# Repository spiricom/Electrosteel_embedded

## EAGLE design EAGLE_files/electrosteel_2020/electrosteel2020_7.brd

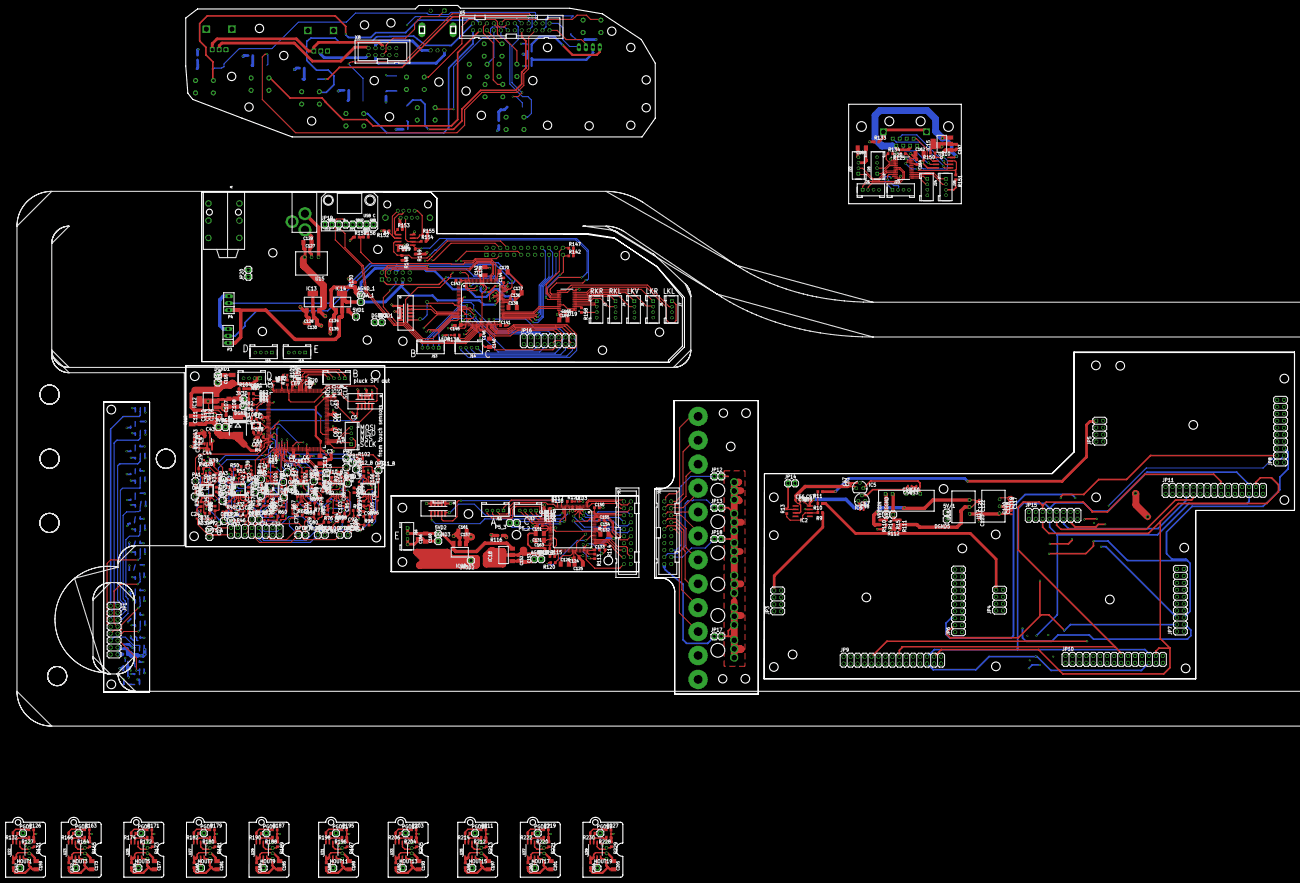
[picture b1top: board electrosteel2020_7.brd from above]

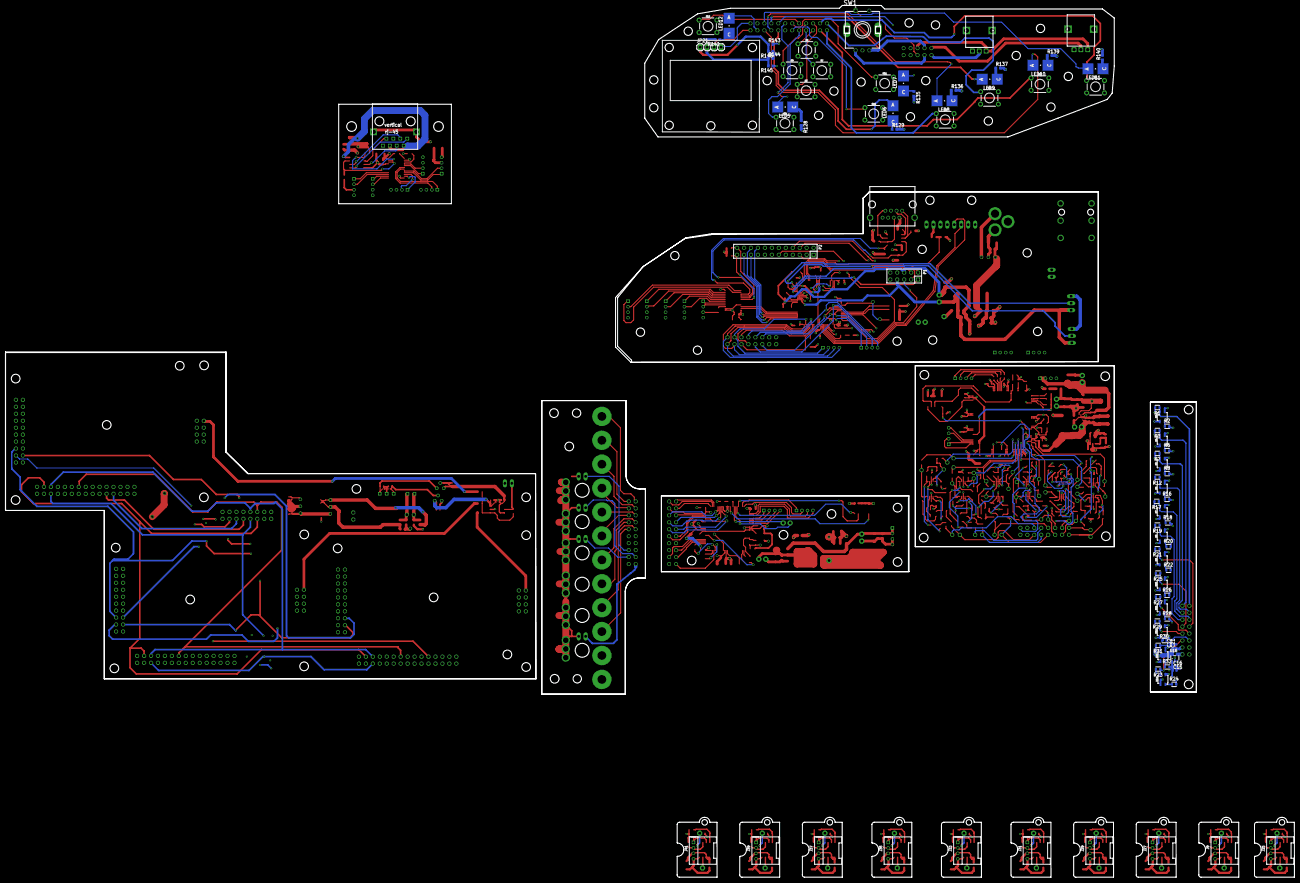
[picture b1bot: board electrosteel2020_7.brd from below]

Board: 4 copper layers, 470.7 x 318.3 mm, 606 parts (90 on the bottom side), 468 nets.

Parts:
3V3A, 3V3A_1, 3V3A_2, 3V3D, 3V3D1, 3V3D2, 5V, 5VD1, 5VD2: 1X01
5V/1: PINHD-1X1; 1X01
AGND: 1X01
AGND_1, AGND_2: 1X01
C1, C2, C3, C4, C5, C11, C12, C13, C14, C15, C20, C22, C23, C24, C25, C26, C27, C28, C29, C30, C31, C32, C33, C34, C35, C36, C37, C38, C39, C40, C41, C42, C43, C44, C45, C46, C47, C48, C49, C50, C55, C56, C57, C60, C61, C62, C63, C70, C71, C72, C73, C74, C75, C76, C77, C78, C79, C80, C81, C82, C83, C84, C85, C86, C87, C88, C89, C90, C91, C92, C93, C94, C95, C96, C97, C98, C99, C100, C101, C102, C103, C104, C105, C106, C113, C117, C118, C122, C123: .1uf; C0402
C6, C7, C8, C9, C10, C51, C52, C53, C54, C58, C59, C66, C67, C68, C69, C116, C119, C120, C121: .01uf; C0201
C16, C21, C64, C65: .01uf; C0402
C17, C18: 18pf; C0603
C19: 2.2uf; C1206
C107, C110: .1uf; C0603
C108, C111, C114: 1uf; C1206
C109, C112, C115: 10uf; SMC_B
C124, C127, C128, C133, C134, C136, C141, C142, C143, C144, C145, C146, C147, C148, C149, C150, C151, C152, C154, C156, C157, C164, C165, C166, C167, C172, C176, C180, C184, C188, C192, C196, C200, C204: .1uf; C0603K
C125, C126, C131, C132, C137, C138, C139, C140, C159, C162, C163, C169, C170, C173, C177, C181, C185, C189, C193, C197, C201, C205: 1uf; C1206K
C129, C130, C135, C153, C160, C161, C168: 10uf; C1206K
C155: 2200pf; C0603K
D3: MBRS340T3; SMC
DGND, DGND1, DGND2, DGND3: 1X01
DGND5: PINHD-1X1; 1X01
HOUT1, HOUT3, HOUT5, HOUT7, HOUT9, HOUT11, HOUT13, HOUT15, HOUT17, HOUT19: 1X01
IC1, IC7, IC8, IC9, IC10, IC17: OPA4344E; TSSOP14
IC2: OPA134D; SO08
IC3: STM32H743ZIT6; QFP50P2200X2200X160-144N
IC4: LMV321M5; SOT23-5
IC5: 78LXX
IC6: 79LXX
IC11: LP5912; 6-WSON
IC12, IC13, IC14, IC15, IC18, IC20: REG1117; SOT223
J1: AUDIO_JACK_TRS_0.25"_PTH_RA; AUDIO_JACK_0.25"_TRS_PTH_RA
J3, J4, J5, J6, J7, J8, J10, J11, J12, J13, J14, J16, J17, J18, J19, J20, J21, J22, J23, J24, J26: 4P-2.0; HW4-2.0
J9, J25, J27, J29, J31, J33, J35, J37, J39, J41: 4P-2.0-90D; HW4-2.0-90D
JP1, JP2, JP15, JP16: PINHD-2X8; 2X08
JP3, JP4, JP5: PINHD-2X4; 2X04
JP6, JP7, JP8: PINHD-2X10; 2X10
JP9, JP10, JP11: 2X15
JP12, JP13, JP14, JP17, JP18, JP20: PINHD-1X2; 1X02
JP19: PINHD-1X8; 1X08
JP21: PINHD-1X4; 1X04
LED1, LED3, LED4: RED; CHIP-LED0603
LED2: GREEN; CHIP-LED0603
LED5, LED6, LED7, LED8, LED9, LED10, LED11, LED12: P-LCC-2
OPT1_A, OPT1_B, OPT2_A, OPT2_B, OPT3_A, OPT3_B, OPT4_A, OPT4_B, OPT5_A, OPT5_B, OPT6_A, OPT6_B, OPT7_A, OPT7_B, OPT8_A, OPT8_B, OPT9_A, OPT9_B, OPT10_A, OPT10_B, OPT11_A, OPT11_B, OPT12_A, OPT12_B: PINHD-1X1; 1X01
P1: P-10-100-2X05_M; DIL-100-2X05_M
P2: P-24-100-2X12_M; DIL-100-2X12_M
P3, P4: M-1X03-SIP-100-40Y; SIP-100-03-40Y
P5_2, P5_3: 1X01
PA0, PA1, PA2, PA3, PA4, PA5, PA6, PA7: PINHD-1X1; 1X01
PB0, PB1: PINHD-1X1; 1X01
PC4, PC5: PINHD-1X1; 1X01
PGO1, PGO3, PGO5, PGO7, PGO9, PGO11, PGO13, PGO15, PGO17, PGO19: 1X01
Q1: 25MHz; NX3225
R1, R3, R7, R12, R17, R19, R21, R23, R25, R27, R29, R31: 10k; RESC1608X60
R2, R6, R8, R16, R18, R20, R22, R24, R26, R28, R30, R32: 100R; RESC1608X60
R4: 47R; R0603
R5: 10k; R0402
R9, R10, R11, R13, R125, R134, R158: 1k; R0603
R14, R15, R86, R87, R108, R132, R145, R146, R166, R174, R182, R190, R198, R206, R214, R222, R230: 0R_DNP; R0603
R33, R34, R38, R39, R45, R46, R50, R51, R55, R56, R60, R61, R66, R67, R71, R72, R76, R77, R88, R89, R93, R94, R98, R99: 20k; R0603
R35, R36, R40, R41, R47, R48, R52, R53, R57, R58, R63, R64, R68, R69, R73, R74, R78, R80, R90, R91, R95, R96, R100, R101: 820R; R0603
R37, R42, R49, R54, R59, R65, R70, R75, R82, R85, R92, R97, R102, R103, R110, R111, R112, R116, R130, R133, R143, R144: 0R; R0603
R43, R44: 100k; R0603
R62, R81, R83, R84, R117, R118, R119, R121, R122, R124: 33R; R0201
R79, R104, R123, R128, R129, R135, R136, R137, R138, R139, R140, R141: 560R; R0603
R105, R106, R107, R109: 33R; R0402
R113, R114, R115, R120: 10k; R0603
R126, R127, R131, R163, R164, R165, R171, R172, R173, R179, R180, R181, R187, R188, R189, R195, R196, R197, R203, R204, R205, R211, R212, R213, R219, R220, R221, R227, R228, R229: 4.7k; R0603
R142, R147, R148, R149, R150, R151, R152, R153, R154, R155, R156, R157: 1.5k; R0603
S1, S2, S3, S4, S5, S6, S7, S8, S9, S10, S11, S12: MOMENTARY-SWITCH-SPST-PTH-6.0MM; TACTILE_SWITCH_PTH_6.0MM
SW1: PEC11R-4215F-S0024
U1, U2: CY8C5868AXI-LP035; TQFP-100-14X14MM
U3, U4, U5, U6, U7, U8, U9, U10, U11, U12, U13, U14: QRE1113
U15, U17, U18: R-78E5.0-1.0; DC-DC_CONVERTER_78XX
U16: TEXAS_TPS2051B; TEXAS_SOT23-5
U19, U20: TCA9548APWR; SOP65P640X120-24N
U22, U23, U25, U27, U29, U31, U33, U35, U37, U39: AS5600; SOIC8-1.27-5X4MM
U$1, U$2: RK09
U$3: CMR0512S3C
U$6: SS-7188VS-A-FLS; SS-7188VS-A-FLS_RJ45
U$9, U$10: P82B96DP,118; SO8
U$11: 2.1MMJACKTHM; PJ-102A
VREGGND: PINHD-1X1; 1X01
VREGIN: PINHD-1X1; 1X01
X1, X2, X3: 3221-10-0300-00
X4: GLX-S-88M
X5: 2524-; PAK100/2500-24
X6, X7: 2520-; PAK100/2500-20
X8: 2510-; PAK100/2500-10

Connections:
3V3: C31.1, C41.1, C43.1, C45.1, C99.1, C101.1, C103.1, C105.1, IC1.4, IC4.5, IC7.4, IC8.4, IC9.4, IC10.4, IC17.4, JP2.14, R43.2
3V3A: 3V3A.1, C65.1, C110.1, C111.1, C112.+, C113.1, C116.1, D3.A, IC3.33, IC11.1, R4.1
3V3A2: 3V3A_2.1, C124.1, C125.1, C152.1, C153.1, IC18.2, IC18.PAD, U1.65
3V3A4: 3V3A_1.1, C134.1, C135.1, C136.1, C137.1, IC14.2, IC14.PAD, P1.7, P3.1, P4.1, U2.65
3V3D2: 3V3D2.1, C133.1, C148.1, C149.1, C150.1, C151.1, C154.1, C157.1, C161.1, IC20.2, IC20.PAD, U1.26, U1.37, U1.50, U1.75, U1.88, U1.100, X3.1
3V3D3: C162.1, C164.1, C167.1, C168.1, IC15.2, IC15.PAD, J20.3, J21.3, J22.3, J23.3, J24.3, J26.3, R125.1, R134.2, R150.2, R151.2, U20.24
3V3D5: 3V3D1.1, C128.1, C130.1, C141.1, C142.1, C143.1, C144.1, C145.1, C146.1, C165.1, C169.1, IC13.2, IC13.PAD, J3.3, J4.3, J5.3, J6.3, J7.3, P1.8, P2.22, R142.2, R147.2, R148.2, R149.2, R158.2, U2.26, U2.37, U2.50, U2.75, U2.88, U2.100, U19.24, X1.1
5VD2: 5VD2.1, C156.1, C160.1, IC18.3, IC20.3, J16.1, J16.2
5VD4: 5VD1.1, C127.1, C129.1, C166.1, IC13.3, IC14.3, J18.1, J18.2, J19.1, J19.2, R152.2, R153.2, R154.2, R155.2, U15.VOUT, U$9.8, X4.2, X4.6
12VD2: JP16.1, U15.VIN, U$11.RING
+1.8V: C26.2, C29.2, C35.2, C39.2, C41.2, C42.1, C43.2, C44.1, C45.2, C46.1, C62.2, C73.2, C77.2, C81.2, C85.2, C89.2, C93.2, C97.2, C99.2, C100.1, C101.2, C102.1, C103.2, C104.1, C105.2, C106.1, IC4.3, IC4.4, R33.1, R39.1, R46.1, R51.1, R56.1, R61.1, R67.1, R72.1, R77.1, R89.1, R94.1, R99.1
+3V3: 3V3D.1, C1.1, C2.1, C3.1, C4.1, C6.1, C7.1, C8.1, C9.1, C10.1, C11.1, C12.1, C13.1, C14.1, C20.1, C55.1, C63.1, C66.1, C67.1, C68.1, C69.1, C107.1, C108.1, C109.+, D3.C, IC3.6, IC3.17, IC3.30, IC3.39, IC3.52, IC3.62, IC3.72, IC3.84, IC3.95, IC3.108, IC3.121, IC3.131, IC3.143, IC3.144, IC11.4, IC12.2, IC12.PAD, R104.1, X2.1
+5V: 5V.1, C114.1, C115.+, IC11.6, IC12.3, J17.1, J17.2
+5V/1: 5V/1.1, C117.1, C119.1, JP6.19, JP7.19, JP8.19, R14.2, U17.VOUT
+9V: C47.1, C51.1, C56.1, C58.1, IC2.7, IC5.OUT
+12V: C118.1, C120.1, C123.1, JP15.1, U17.VIN, U18.VIN
-9V: C48.2, C52.2, C57.2, C59.2, IC2.4, IC6.OUT
AGND: AGND.1, C32.2, C42.2, C44.2, C46.2, C64.2, C65.2, C100.2, C102.2, C104.2, C106.2, C110.2, C111.2, C112.-, C113.2, C116.2, IC1.11, IC3.31, IC4.2, IC7.11, IC8.11, IC9.11, IC10.11, IC11.5, IC11.PAD, IC17.11, JP2.13, JP2.15, R44.1, R103.2
AGND2: AGND_2.1, C124.2, C125.2, C126.2, C152.2, C153.2, C163.2, IC18.1, JP12.2, JP13.2, JP17.2, JP18.2, R116.1, U1.64, X6.20, X7.13, X7.14, X7.20
AGND4: AGND_1.1, C134.2, C135.2, C136.2, C137.2, C138.2, C170.2, IC14.1, P1.6, P3.3, P4.3, R130.1, U2.64
AGND5: C47.2, C48.1, C49.1, C50.2, C51.2, C52.1, C53.2, C54.1, C56.2, C57.1, C58.2, C59.1, IC2.3, IC5.GND, IC6.GND, JP3.3, JP3.4, JP3.5, JP3.6, JP4.3, JP4.4, JP4.5, JP4.6, JP5.3, JP5.4, JP5.5, JP5.6, JP14.2, U$3.P$4
BOTTOMWIPER1: R114.1, U1.77
BOTTOMWIPER2: U1.78, X7.17
CGND: C15.2, C16.2, C21.2, C22.2, JP1.13, JP1.15, U3.2, U3.4, U4.2, U4.4, U5.2, U5.4, U6.2, U6.4, U7.2, U7.4, U8.2, U8.4, U9.2, U9.4, U10.2, U10.4, U11.2, U11.4, U12.2, U12.4, U13.2, U13.4, U14.2, U14.4, U16.2
CMOD: C155.1, U1.93
DGND: C1.2, C2.2, C3.2, C4.2, C5.2, C6.2, C7.2, C8.2, C9.2, C10.2, C11.2, C12.2, C13.2, C14.2, C17.2, C18.2, C19.2, C20.2, C55.2, C63.2, C66.2, C67.2, C68.2, C69.2, C107.2, C108.2, C109.-, C114.2, C115.-, DGND.1, DGND1.1, IC3.16, IC3.38, IC3.51, IC3.61, IC3.83, IC3.94, IC3.107, IC3.120, IC3.130, IC12.1, J17.3, J17.4, LED1.C, LED2.C, Q1.2, Q1.4, R5.2, R103.1, X2.3, X2.5, X2.9
DGND2: C131.2, C132.2, C133.2, C148.2, C149.2, C150.2, C151.2, C154.2, C155.2, C156.2, C157.2, C160.2, C161.2, DGND3.1, IC20.1, J16.3, J16.4, LED3.C, R116.2, U1.10, U1.12, U1.13, U1.14, U1.38, U1.66, U1.87, X3.3, X3.5, X3.7, X3.9
DGND4: C117.2, C118.2, C119.2, C120.2, C123.2, DGND5.1, JP6.20, JP7.20, JP8.20, JP9.20, JP9.22, JP10.22, JP11.20, JP15.2, R15.2, R112.2, U17.GND
DGND5: C127.2, C128.2, C129.2, C130.2, C139.2, C140.2, C141.2, C142.2, C143.2, C144.2, C145.2, C146.2, C165.2, C166.2, C169.2, DGND2.1, IC13.1, J3.4, J4.4, J5.4, J6.4, J7.4, J18.3, J18.4, J19.3, J19.4, JP16.2, JP19.8, LED4.C, P1.9, P1.10, P2.13, R130.2, R157.1, U2.10, U2.12, U2.13, U2.14, U2.38, U2.66, U2.87, U15.GND, U19.1, U19.2, U19.12, U19.21, U$9.4, U$11.TIP, X1.3, X1.5, X1.7, X1.9, X4.5, X4.8, X4.S1, X4.S2
DM: JP19.4, U2.36
DP: JP19.3, U2.35
EGND: R128.2, R129.2, R135.2, R136.2, R137.2, R139.2, R140.2, R141.2, R144.2, R146.1, S1.3, S2.3, S3.3, S4.3, S5.3, S6.3, S7.3, S8.3, S9.3, S10.3, S11.3, S12.3, SW1.2, SW1.C, X5.13, X8.9, X8.10
GND-ISO: C162.2, C164.2, C167.2, C168.2, IC15.1, J20.4, J21.4, J22.4, J23.4, J24.4, J26.4, R133.1, U20.2, U20.12, U20.21, U$6.P$5, U$6.P$8, U$10.4
MIDBOTTOMWIPER1: R120.2, U1.83
MIDBOTTOMWIPER2: U1.79, X7.15
MIDDLEWIPER1: R115.1, U1.45
MIDDLEWIPER2: U1.80, X7.18
MSPI1_MISO: J11.3, U1.27
MSPI1_MOSI: J11.4, R119.1
MSPI1_NSS: J11.2, R118.1
MSPI1_SCK: J11.1, R117.1
MSPI2_MISO: J12.3, U1.33
MSPI2_MOSI: J12.4, R124.1
MSPI2_NSS: J12.2, R122.1
MSPI2_SCK: J12.1, R121.1
unnamed: R6.1, U4.1
unnamed: R2.1, U3.1
unnamed: C121.1, C122.1, R110.2, U18.VOUT
unnamed: C121.2, C122.2, R111.2, R112.1, U18.GND
unnamed: LED2.A, R79.2
unnamed: IC3.134, R79.1
unnamed: R8.1, U5.1
unnamed: IC3.4, R81.2
unnamed: U1.3, X7.1
unnamed: JP17.1, X6.19
unnamed: JP18.1, X6.18
unnamed: IC3.3, R83.2
unnamed: JP13.1, X6.17
unnamed: JP12.1, X6.16
unnamed: LED3.A, R123.2
unnamed: IC3.5, R84.2
unnamed: R123.1, U1.17
unnamed: IC3.1, R62.2
unnamed: P5_2.1, U1.18
unnamed: P5_3.1, U1.19
unnamed: C138.1, U2.63
unnamed: C170.1, U2.76
unnamed: U1.2, X7.2
unnamed: U1.1, X7.3
unnamed: JP3.8, R9.1
unnamed: JP4.8, R10.1
unnamed: JP5.8, R11.1
unnamed: IC2.2, R9.2, R10.2, R11.2, R13.1
unnamed: C50.1, C53.1, IC5.IN, U$3.P$5
unnamed: C60.1, C61.2, R55.1
unnamed: IC2.6, JP14.1, R13.2
unnamed: R16.1, U6.1
unnamed: C49.2, C54.2, IC6.IN, U$3.P$3
unnamed: R18.1, U7.1
unnamed: R20.1, U8.1
unnamed: R22.1, U9.1
unnamed: R24.1, U14.1
unnamed: R26.1, U10.1
unnamed: R28.1, U11.1
unnamed: R30.1, U12.1
unnamed: R32.1, U13.1
unnamed: C27.1, C28.2, R38.1
unnamed: IC3.138, R5.1
unnamed: C28.1, IC17.10, R39.2
unnamed: IC17.8, IC17.9, R38.2, R40.2
unnamed: C29.1, IC17.12, R41.1
unnamed: C30.1, R40.1, R41.2
unnamed: C33.1, C34.2, R45.1
unnamed: C34.1, IC1.3, R46.2
unnamed: IC1.1, IC1.2, R45.2, R47.2
unnamed: C35.1, IC1.5, R48.1
unnamed: C36.1, R47.1, R48.2
unnamed: C37.1, C38.2, R50.1
unnamed: C38.1, IC1.10, R51.2
unnamed: IC1.8, IC1.9, R50.2, R52.2
unnamed: C39.1, IC1.12, R53.1
unnamed: C40.1, R52.1, R53.2
unnamed: C61.1, IC7.3, R56.2
unnamed: IC7.1, IC7.2, R55.2, R57.2
unnamed: LED1.A, R104.2
unnamed: C62.1, IC7.5, R58.1
unnamed: C70.1, R57.1, R58.2
unnamed: C71.1, C72.2, R60.1
unnamed: C72.1, IC7.10, R61.2
unnamed: IC7.8, IC7.9, R60.2, R63.2
unnamed: C73.1, IC7.12, R64.1
unnamed: C23.1, C24.2, R34.1
unnamed: C24.1, IC17.3, R33.2
unnamed: C74.1, R63.1, R64.2
unnamed: IC17.1, IC17.2, R34.2, R35.2
unnamed: C26.1, IC17.5, R36.1
unnamed: C25.1, R35.1, R36.2
unnamed: C75.1, C76.2, R66.1
unnamed: C76.1, IC8.3, R67.2
unnamed: IC8.1, IC8.2, R66.2, R68.2
unnamed: C77.1, IC8.5, R69.1
unnamed: C78.1, R68.1, R69.2
unnamed: C79.1, C80.2, R71.1
unnamed: C80.1, IC8.10, R72.2
unnamed: IC8.8, IC8.9, R71.2, R73.2
unnamed: C81.1, IC8.12, R74.1
unnamed: C82.1, R73.1, R74.2
unnamed: C83.1, C84.2, R76.1
unnamed: C84.1, IC9.3, R77.2
unnamed: IC9.1, IC9.2, R76.2, R78.2
unnamed: C85.1, IC9.5, R80.1
unnamed: C86.1, R78.1, R80.2
unnamed: C87.1, C88.2, R88.1
unnamed: C88.1, IC9.10, R89.2
unnamed: IC9.8, IC9.9, R88.2, R90.2
unnamed: C89.1, IC9.12, R91.1
unnamed: C90.1, R90.1, R91.2
unnamed: C91.1, C92.2, R93.1
unnamed: C92.1, IC10.3, R94.2
unnamed: IC10.1, IC10.2, R93.2, R95.2
unnamed: C93.1, IC10.5, R96.1
unnamed: C94.1, R95.1, R96.2
unnamed: C95.1, C96.2, R98.1
unnamed: C96.1, IC10.10, R99.2
unnamed: IC10.8, IC10.9, R98.2, R100.2
unnamed: C97.1, IC10.12, R101.1
unnamed: C98.1, R100.1, R101.2
unnamed: C31.2, C32.1, IC4.1, R43.1, R44.2
unnamed: R15.1, R111.1, U$3.P$2, VREGGND.1
unnamed: R14.1, R110.1, U$3.P$1, VREGIN.1
unnamed: U1.99, X7.4
unnamed: U1.98, X7.5
unnamed: U1.6, X7.6
unnamed: U1.7, X7.7
unnamed: C126.1, U1.63
unnamed: U1.8, X7.8
unnamed: U1.97, X7.11
unnamed: U1.9, X7.9
unnamed: U1.95, X7.10
unnamed: C163.1, U1.46
unnamed: U1.96, X7.12
unnamed: R117.2, U1.24
unnamed: R118.2, U1.25
unnamed: R119.2, U1.28
unnamed: J3.1, U19.5
unnamed: R121.2, U1.31
unnamed: R122.2, U1.32
unnamed: J3.2, U19.4
unnamed: R124.2, U1.34
unnamed: J4.1, U19.7
unnamed: J4.2, U19.6
unnamed: J5.1, U19.9
unnamed: J5.2, U19.8
unnamed: J6.1, U19.11
unnamed: J6.2, U19.10
unnamed: J7.1, U19.14
unnamed: J7.2, U19.13
unnamed: R125.2, U20.1
unnamed: J20.1, U20.5
unnamed: J20.2, U20.4
unnamed: J21.1, U20.7
unnamed: J21.2, U20.6
unnamed: J22.1, U20.9
unnamed: J22.2, U20.8
unnamed: J23.1, U20.11
unnamed: LED4.A, R138.2
unnamed: S1.1, X5.1
unnamed: J23.2, U20.10
unnamed: J24.1, U20.14
unnamed: J24.2, U20.13
unnamed: U$6.P$4, U$10.3
unnamed: R150.1, U20.23, U$10.1
unnamed: U$6.P$1, U$10.5
unnamed: R126.1, R132.2, U22.8
unnamed: J25.2, R131.2, U22.6
unnamed: J25.1, R127.2, U22.7
unnamed: C147.1, C159.1, J25.3, R126.2, R127.1, R131.1, U22.1, U22.2
unnamed: C147.2, C159.2, J25.4, R132.1, U22.4
unnamed: PGO1.1, U22.5
unnamed: J26.1, U20.16
unnamed: J26.2, U20.15
unnamed: HOUT1.1, U22.3
unnamed: J1.TIP, JP20.1
unnamed: J1.SLEEVE, JP20.2
unnamed: S2.1, X5.2
unnamed: S3.1, X5.3
unnamed: R153.1, U$9.5, X4.3
unnamed: S4.1, X5.4
unnamed: R154.1, U$9.2, X4.4
unnamed: R155.1, U$9.3, X4.7
unnamed: U$6.P$3, U$10.6
unnamed: U$6.P$7, U$10.2
unnamed: R133.2, U$6.P$9, U$6.P$10
unnamed: R151.1, U20.22, U$10.7
unnamed: R134.1, U20.3
unnamed: R152.1, U$9.6, X4.1
unnamed: S5.1, X5.5
unnamed: IC15.3, U$6.P$2, U$6.P$6, U$10.8
unnamed: S6.1, X5.6
unnamed: S7.1, X5.7
unnamed: S8.1, X5.8
unnamed: S9.1, X5.9
unnamed: S12.1, X5.10
unnamed: S10.1, X5.11
unnamed: S11.1, X5.12
unnamed: R148.1, U19.16, U$9.7
unnamed: LED5.A, X5.14
unnamed: LED6.A, X5.15
unnamed: LED7.A, X5.16
unnamed: LED8.A, X5.17
unnamed: LED9.A, X5.18
unnamed: LED10.A, X5.19
unnamed: LED11.A, X5.20
unnamed: LED12.A, X5.21
unnamed: R149.1, U19.15, U$9.1
unnamed: LED5.C, R128.1
unnamed: LED6.C, R129.1
unnamed: LED7.C, R135.1
unnamed: LED8.C, R136.1
unnamed: LED9.C, R137.1
unnamed: LED10.C, R139.1
unnamed: LED11.C, R140.1
unnamed: LED12.C, R141.1
unnamed: P2.23, R142.1, U19.18
unnamed: U$1.2-09, X8.1
unnamed: U$2.2-09, X8.2
unnamed: SW1.A, X8.3
unnamed: SW1.B, X8.4
unnamed: SW1.1, X8.5
unnamed: U$1.3-09, U$2.3-09, X8.6
unnamed: U$1.1-09, U$2.1-09, X8.7
unnamed: JP21.3, X5.23
unnamed: JP21.4, X5.24
unnamed: JP21.1, R143.1, R146.2
unnamed: JP21.2, R144.1, R145.2
unnamed: R143.2, R145.1, X5.22, X8.8
unnamed: P2.24, R147.1, U19.17
unnamed: P1.1, U2.71
unnamed: P1.2, U2.72
unnamed: P3.2, U2.73
unnamed: P4.2, U2.74
unnamed: P1.3, U2.80
unnamed: P1.4, U2.81
unnamed: P1.5, U2.34
unnamed: R158.1, U19.3
unnamed: R138.1, U2.33
unnamed: P2.1, U2.32
unnamed: P2.2, U2.31
unnamed: P2.3, U2.28
unnamed: P2.4, U2.27
unnamed: P2.5, U2.25
unnamed: P2.6, U2.24
unnamed: P2.7, U2.23
unnamed: P2.8, U2.22
unnamed: P2.21, U2.51
unnamed: P2.20, U2.52
unnamed: P2.19, U2.53
unnamed: P2.18, U2.54
unnamed: P2.9, U2.99
unnamed: P2.10, U2.98
unnamed: P2.11, U2.97
unnamed: P2.12, U2.96
unnamed: P2.14, U2.67
unnamed: P2.15, U2.68
unnamed: P2.16, U2.69
unnamed: P2.17, U2.70
unnamed: R163.1, R166.2, U23.8
unnamed: J9.2, R165.2, U23.6
unnamed: J9.1, R164.2, U23.7
unnamed: C172.1, C173.1, J9.3, R163.2, R164.1, R165.1, U23.1, U23.2
unnamed: C172.2, C173.2, J9.4, R166.1, U23.4
unnamed: PGO3.1, U23.5
unnamed: HOUT3.1, U23.3
unnamed: R171.1, R174.2, U25.8
unnamed: J27.2, R173.2, U25.6
unnamed: J27.1, R172.2, U25.7
unnamed: C176.1, C177.1, J27.3, R171.2, R172.1, R173.1, U25.1, U25.2
unnamed: C176.2, C177.2, J27.4, R174.1, U25.4
unnamed: PGO5.1, U25.5
unnamed: HOUT5.1, U25.3
unnamed: R179.1, R182.2, U27.8
unnamed: J29.2, R181.2, U27.6
unnamed: J29.1, R180.2, U27.7
unnamed: C180.1, C181.1, J29.3, R179.2, R180.1, R181.1, U27.1, U27.2
unnamed: C180.2, C181.2, J29.4, R182.1, U27.4
unnamed: PGO7.1, U27.5
unnamed: HOUT7.1, U27.3
unnamed: R187.1, R190.2, U29.8
unnamed: J31.2, R189.2, U29.6
unnamed: J31.1, R188.2, U29.7
unnamed: C184.1, C185.1, J31.3, R187.2, R188.1, R189.1, U29.1, U29.2
unnamed: C184.2, C185.2, J31.4, R190.1, U29.4
unnamed: PGO9.1, U29.5
unnamed: HOUT9.1, U29.3
unnamed: R195.1, R198.2, U31.8
unnamed: J33.2, R197.2, U31.6
unnamed: J33.1, R196.2, U31.7
unnamed: C188.1, C189.1, J33.3, R195.2, R196.1, R197.1, U31.1, U31.2
unnamed: C188.2, C189.2, J33.4, R198.1, U31.4
unnamed: PGO11.1, U31.5
unnamed: HOUT11.1, U31.3
unnamed: R203.1, R206.2, U33.8
unnamed: J35.2, R205.2, U33.6
unnamed: J35.1, R204.2, U33.7
unnamed: C192.1, C193.1, J35.3, R203.2, R204.1, R205.1, U33.1, U33.2
unnamed: C192.2, C193.2, J35.4, R206.1, U33.4
unnamed: PGO13.1, U33.5
unnamed: HOUT13.1, U33.3
unnamed: R211.1, R214.2, U35.8
unnamed: J37.2, R213.2, U35.6
unnamed: J37.1, R212.2, U35.7
unnamed: C196.1, C197.1, J37.3, R211.2, R212.1, R213.1, U35.1, U35.2
unnamed: C196.2, C197.2, J37.4, R214.1, U35.4
unnamed: PGO15.1, U35.5
unnamed: HOUT15.1, U35.3
unnamed: R219.1, R222.2, U37.8
unnamed: J39.2, R221.2, U37.6
unnamed: J39.1, R220.2, U37.7
unnamed: C200.1, C201.1, J39.3, R219.2, R220.1, R221.1, U37.1, U37.2
unnamed: C200.2, C201.2, J39.4, R222.1, U37.4
unnamed: PGO17.1, U37.5
unnamed: HOUT17.1, U37.3
unnamed: R227.1, R230.2, U39.8
unnamed: J41.2, R229.2, U39.6
unnamed: J41.1, R228.2, U39.7
unnamed: C204.1, C205.1, J41.3, R227.2, R228.1, R229.1, U39.1, U39.2
unnamed: C204.2, C205.2, J41.4, R230.1, U39.4
unnamed: PGO19.1, U39.5
unnamed: HOUT19.1, U39.3
OPT1: JP1.1, R1.1, U3.3
OPT1_A: C23.2, JP2.1, OPT1_A.1
OPT1_B: C25.2, IC17.6, IC17.7, OPT1_B.1, R37.2
OPT2: JP1.2, R3.1, U4.3
OPT2_A: C27.2, JP2.2, OPT2_A.1
OPT2_B: C30.2, IC17.13, IC17.14, OPT2_B.1, R42.2
OPT3: JP1.3, R7.1, U5.3
OPT3_A: C33.2, JP2.3, OPT3_A.1
OPT3_B: C36.2, IC1.6, IC1.7, OPT3_B.1, R49.2
OPT4: JP1.4, R12.1, U6.3
OPT4_A: C37.2, JP2.4, OPT4_A.1
OPT4_B: C40.2, IC1.13, IC1.14, OPT4_B.1, R54.2
OPT5: JP1.5, R17.1, U7.3
OPT5_A: C60.2, JP2.5, OPT5_A.1
OPT5_B: C70.2, IC7.6, IC7.7, OPT5_B.1, R59.2
OPT6: JP1.6, R19.1, U8.3
OPT6_A: C71.2, JP2.6, OPT6_A.1
OPT6_B: C74.2, IC7.13, IC7.14, OPT6_B.1, R65.2
OPT7: JP1.7, R21.1, U9.3
OPT7_A: C75.2, JP2.7, OPT7_A.1
OPT7_B: C78.2, IC8.6, IC8.7, OPT7_B.1, R70.2
OPT8: JP1.8, R25.1, U10.3
OPT8_A: C79.2, JP2.8, OPT8_A.1
OPT8_B: C82.2, IC8.13, IC8.14, OPT8_B.1, R75.2
OPT9: JP1.9, R27.1, U11.3
OPT9_A: C83.2, JP2.9, OPT9_A.1
OPT9_B: C86.2, IC9.6, IC9.7, OPT9_B.1, R85.2
OPT10: JP1.10, R29.1, U12.3
OPT10_A: C87.2, JP2.10, OPT10_A.1
OPT10_B: C90.2, IC9.13, IC9.14, OPT10_B.1, R92.2
OPT11: JP1.11, R31.1, U13.3
OPT11_A: C91.2, JP2.11, OPT11_A.1
OPT11_B: C94.2, IC10.6, IC10.7, OPT11_B.1, R97.2
OPT12: JP1.12, R23.1, U14.3
OPT12_A: C95.2, JP2.12, OPT12_A.1
OPT12_B: C98.2, IC10.13, IC10.14, OPT12_B.1, R102.2
OPT_PWR: C21.1, C22.1, JP1.14, R1.2, R3.2, R7.2, R12.2, R17.2, R19.2, R21.2, R23.2, R25.2, R27.2, R29.2, R31.2, U16.5
OPT_PWR_EN: JP1.16, U16.4
OPT_PWR_EN_A: IC3.55, JP2.16
OPT_PWR_SW: C15.1, C16.1, R2.2, R6.2, R8.2, R16.2, R18.2, R20.2, R22.2, R24.2, R26.2, R28.2, R30.2, R32.2, U16.1
OSC1: C17.1, IC3.23, Q1.1
OSC2: C18.1, IC3.24, Q1.3
PA0: IC3.34, PA0.1, R37.1
PA1: IC3.35, PA1.1, R42.1
PA2: IC3.36, PA2.1, R49.1
PA3: IC3.37, PA3.1, R54.1
PA4: IC3.40, PA4.1, R59.1
PA5: IC3.41, PA5.1, R65.1
PA6: IC3.42, PA6.1, R70.1
PA7: IC3.43, PA7.1, R75.1
PB0: IC3.46, PB0.1, R97.1
PB1: IC3.47, PB1.1, R102.1
PB12: IC3.73, J10.2
PB13: IC3.74, J10.1
PB14: IC3.75, J10.3
PB15: IC3.76, J10.4
PC4: IC3.44, PC4.1, R85.1
PC5: IC3.45, PC5.1, R92.1
PD7: IC3.123, R107.2
PD11: IC3.80, R82.2, R86.2, R87.2, R108.2
PG9: IC3.124, R109.1
PG10: IC3.125, R106.1
PG11: IC3.126, R105.1
SAI1_FS_A: R82.1, R83.1
SAI1_MCLK_A: R62.1, R87.1
SAI1_SCK_A: R81.1, R86.1
SAI1_SD_A: R84.1, R108.1
SCL_B: U2.56, U19.22
SDA_B: U2.55, U19.23
SPI1_CS: JP9.28, JP10.28, JP11.28, JP15.5
SPI1_CS_B: JP16.9, U2.45
SPI1_MISO: JP9.25, JP10.25, JP11.25, JP15.7
SPI1_MISO_B: JP16.11, U2.42
SPI1_MISO_OUT: J8.3, R109.2
SPI1_MOSI: JP9.26, JP10.26, JP11.26, JP15.8
SPI1_MOSI_B: JP16.12, U2.43
SPI1_MOSI_OUT: J8.4, R107.1
SPI1_NSS_OUT: J8.2, R106.2
SPI1_SCK: JP9.18, JP10.18, JP11.18, JP15.6
SPI1_SCK_OUT: J8.1, R105.2
SPI1_SCLK_B: JP16.10, U2.44
SPI2_CS: JP6.3, JP7.3, JP8.3, JP15.13
SPI2_CS_B: J14.2, JP16.13, U2.49
SPI2_MISO: JP6.5, JP7.5, JP8.5, JP15.15
SPI2_MISO_B: J14.3, JP16.15, U2.46
SPI2_MOSI: JP6.6, JP7.6, JP8.6, JP15.16
SPI2_MOSI_B: J14.4, JP16.16, U2.47
SPI2_SCK: JP6.4, JP7.4, JP8.4, JP15.14
SPI2_SCLK_B: J14.1, JP16.14, U2.48
SPI3_CS_B: J13.2, JP16.5, U2.19
SPI3_MISO_B: J13.3, JP16.7, U2.16
SPI3_MOSI_B: J13.4, JP16.8, U2.17
SPI3_SCLK_B: J13.1, JP16.6, U2.18
SPI5_CS: JP9.9, JP10.9, JP11.9, JP15.9
SPI5_MISO: JP9.7, JP10.7, JP11.7, JP15.11
SPI5_MOSI: JP9.8, JP10.8, JP11.8, JP15.12
SPI5_SCK: JP9.10, JP10.10, JP11.10, JP15.10
SWCLK: IC3.109, X2.4
SWDIO: IC3.105, X2.2
SWDRESET: C5.1, IC3.25, X2.10
SWD_CK_2: U1.21, X3.4
SWD_CK_3: U2.21, X1.4
SWD_IO_2: U1.20, X3.2
SWD_IO_3: U2.20, X1.2
SWO: IC3.133, X2.6
TOPWIPER1: R113.1, U1.74
TOPWIPER2: U1.73, X7.19
USB_VBUS: R156.1, R157.2, U2.77
VBUS: JP19.7, R156.2
VCAP1: C19.1, IC3.71, IC3.106
VCCD0_2: C131.1, C132.1, U1.39, U1.86
VCCD0_3: C139.1, C140.1, U2.39, U2.86
VOUT1: R113.2, U1.71
VOUT2: R114.2, U1.72
VOUT3: R115.2, U1.51
VOUT4: R120.1, U1.52
VREF: C64.1, IC3.32, R4.2
XRES_2: U1.15, X3.10
XRES_3: U2.15, X1.10

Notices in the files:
parts and their libraries:
SparkFun-IC-Microcontroller: Licensing: Creative Commons ShareAlike 4.0 International - https://creativecommons.org/licenses/by-sa/4.0
con-headers-jp: Copyright (C) 2008, Bob Starr
